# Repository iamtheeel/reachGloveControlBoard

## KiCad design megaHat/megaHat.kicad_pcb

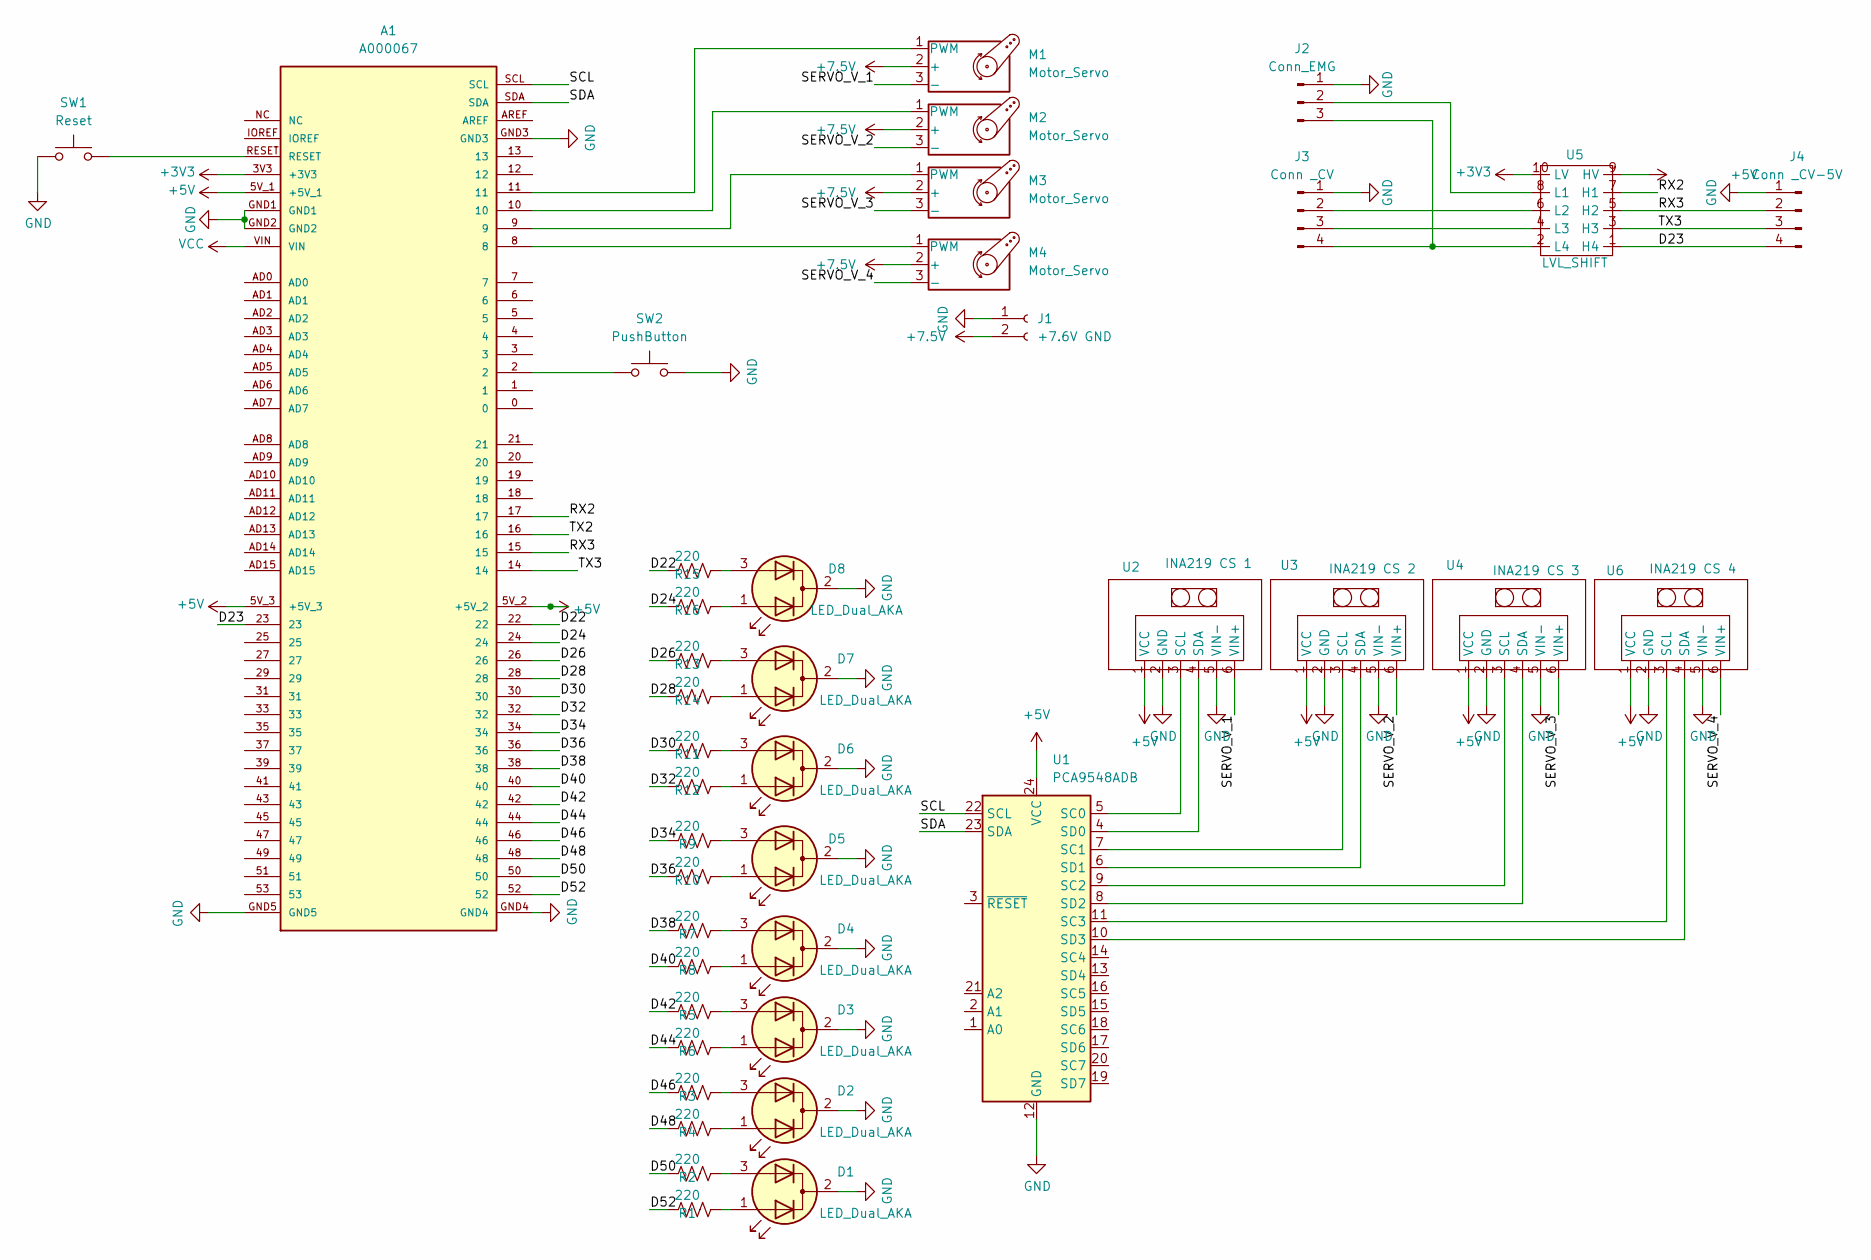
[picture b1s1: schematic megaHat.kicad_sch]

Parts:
A1: A000067; MODULE_A000067; PARTREV 3
D1, D2, D3, D4, D5, D6, D7, D8: LED_Dual_AKA; LED_Rectangular_W5.0mm_H2.0mm-3Pins
J1: +7.6V GND; TerminalBlock_Phoenix_MKDS-1,5-2_1x02_P5.00mm_Horizontal
J2: Conn_EMG; PinHeader_1x03_P2.54mm_Vertical
J3: Conn _CV; PinHeader_1x04_P2.54mm_Vertical
J4: Conn _CV-5V; PinHeader_1x04_P2.54mm_Vertical
M1, M2, M3, M4: Motor_Servo; PinHeader_1x03_P2.54mm_Vertical
R1, R2, R3, R4, R5, R6, R7, R8, R9, R10, R11, R12, R13, R14, R15, R16: 220; R_Axial_DIN0204_L3.6mm_D1.6mm_P2.54mm_Vertical
SW1: Reset; SW_PUSH_6mm
SW2: PushButton; SW_PUSH_6mm
U1: PCA9548ADB; TCA9548A_MultiplexerBreakout
U2: INA219 CS 1; INA219_CS
U3: INA219 CS 2; INA219_CS
U4: INA219 CS 3; INA219_CS
U5: LVL_SHIFT; Pololu-LLShift_2595
U6: INA219 CS 4; INA219_CS

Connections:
+3V3: A1.3V3 (+3V3), U5.10 (LV)
+5V: A1.5V_1 (+5V_1), A1.5V_2 (+5V_2), A1.5V_3 (+5V_3), U1.24 (VCC), U2.1 (VCC), U3.1 (VCC), U4.1 (VCC), U5.9 (HV), U6.1 (VCC)
+7.5V: J1.2, M1.2 (+), M2.2 (+), M3.2 (+), M4.2 (+)
/D22: A1.22, R15.2
/D23: A1.23, J4.4, U5.1 (H4)
/D24: A1.24, R16.2
/D26: A1.26, R13.2
/D28: A1.28, R14.2
/D30: A1.30, R11.2
/D32: A1.32, R12.2
/D34: A1.34, R9.2
/D36: A1.36, R10.2
/D38: A1.38, R7.2
/D40: A1.40, R8.2
/D42: A1.42, R5.2
/D44: A1.44, R6.2
/D46: A1.46, R3.2
/D48: A1.48, R4.2
/D50: A1.50, R2.2
/D52: A1.52, R1.2
/RX2: A1.17, U5.7 (H1)
/RX3: A1.15, J4.2, U5.5 (H2)
/SCL: A1.SCL, U1.22 (SCL)
/SDA: A1.SDA, U1.23 (SDA)
/SERVO_V_1: M1.3 (-), U2.6 (VIN+)
/SERVO_V_2: M2.3 (-), U3.6 (VIN+)
/SERVO_V_3: M3.3 (-), U4.6 (VIN+)
/SERVO_V_4: M4.3 (-), U6.6 (VIN+)
/TX2: A1.16
/TX3: A1.14, J4.3, U5.3 (H3)
GND: A1.GND1, A1.GND2, A1.GND3, A1.GND4, A1.GND5, D1.2 (K), D2.2 (K), D3.2 (K), D4.2 (K), D5.2 (K), D6.2 (K), D7.2 (K), D8.2 (K), J1.1, J2.1, J3.1, J4.1, SW1.1, SW2.2, U1.12 (GND), U2.2 (GND), U2.5 (VIN-), U3.2 (GND), U3.5 (VIN-), U4.2 (GND), U4.5 (VIN-), U6.2 (GND), U6.5 (VIN-)
unnamed: A1.2, SW2.1
unnamed: A1.RESET, SW1.2
unnamed: D1.1 (A1), R1.1
unnamed: D1.3 (A2), R2.1
unnamed: D2.1 (A1), R4.1
unnamed: D2.3 (A2), R3.1
unnamed: D3.1 (A1), R6.1
unnamed: D3.3 (A2), R5.1
unnamed: D4.1 (A1), R8.1
unnamed: D4.3 (A2), R7.1
unnamed: D5.1 (A1), R10.1
unnamed: D5.3 (A2), R9.1
unnamed: D6.1 (A1), R12.1
unnamed: D6.3 (A2), R11.1
unnamed: D7.1 (A1), R14.1
unnamed: D7.3 (A2), R13.1
unnamed: D8.1 (A1), R16.1
unnamed: D8.3 (A2), R15.1
unnamed: J2.2, U5.8 (L1)
unnamed: J2.3, J3.4, U5.2 (L4)
unnamed: J3.2, U5.6 (L2)
unnamed: J3.3, U5.4 (L3)
unnamed: A1.11, M1.1 (PWM)
unnamed: A1.10, M2.1 (PWM)
unnamed: A1.9, M3.1 (PWM)
unnamed: A1.8, M4.1 (PWM)
unnamed: U1.5 (SC0), U2.3 (SCL)
unnamed: U1.7 (SC1), U3.3 (SCL)
unnamed: U1.9 (SC2), U4.3 (SCL)
unnamed: U1.11 (SC3), U6.3 (SCL)
unnamed: U1.4 (SD0), U2.4 (SDA)
unnamed: U1.6 (SD1), U3.4 (SDA)
unnamed: U1.8 (SD2), U4.4 (SDA)
unnamed: U1.10 (SD3), U6.4 (SDA)
VCC: A1.VIN

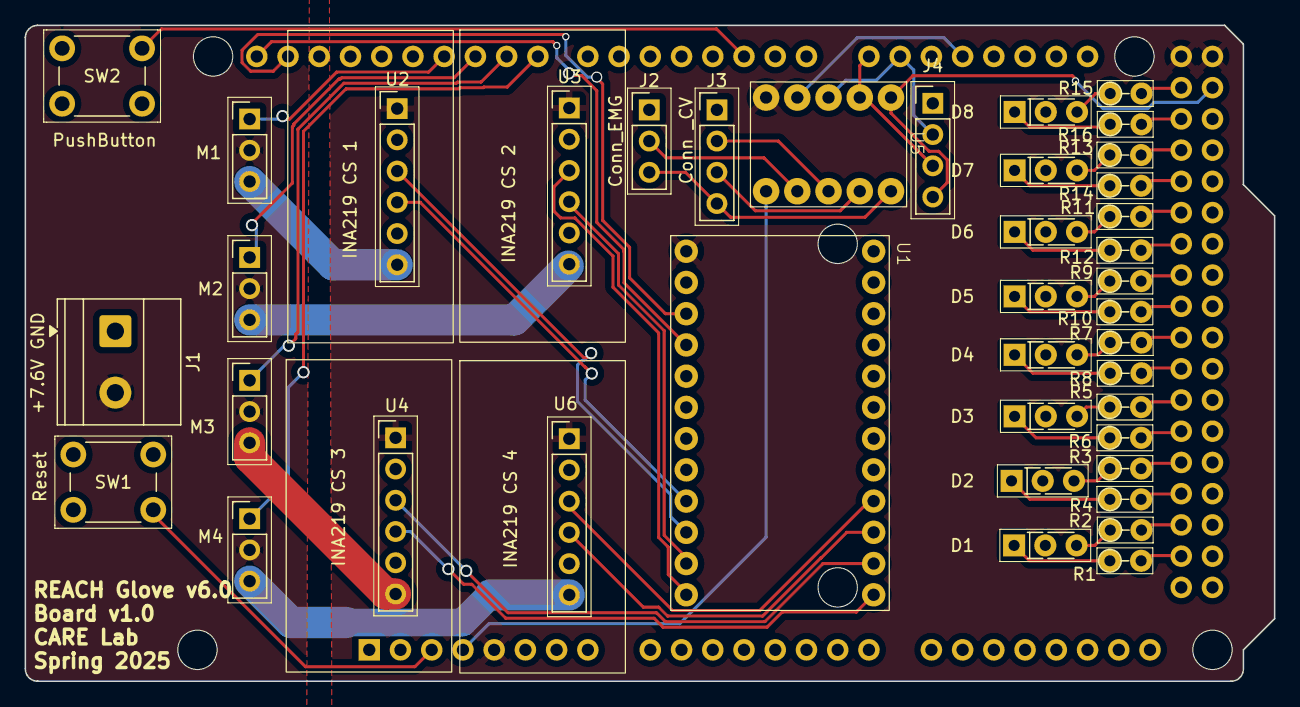
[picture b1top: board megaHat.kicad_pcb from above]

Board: 2 copper layers, 101.6 x 53.3 mm, 41 parts (0 on the bottom side), 64 nets.

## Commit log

2025-05-23 First Light
2025-05-23 added componentss
2025-07-20 Vias large, added images for fab
